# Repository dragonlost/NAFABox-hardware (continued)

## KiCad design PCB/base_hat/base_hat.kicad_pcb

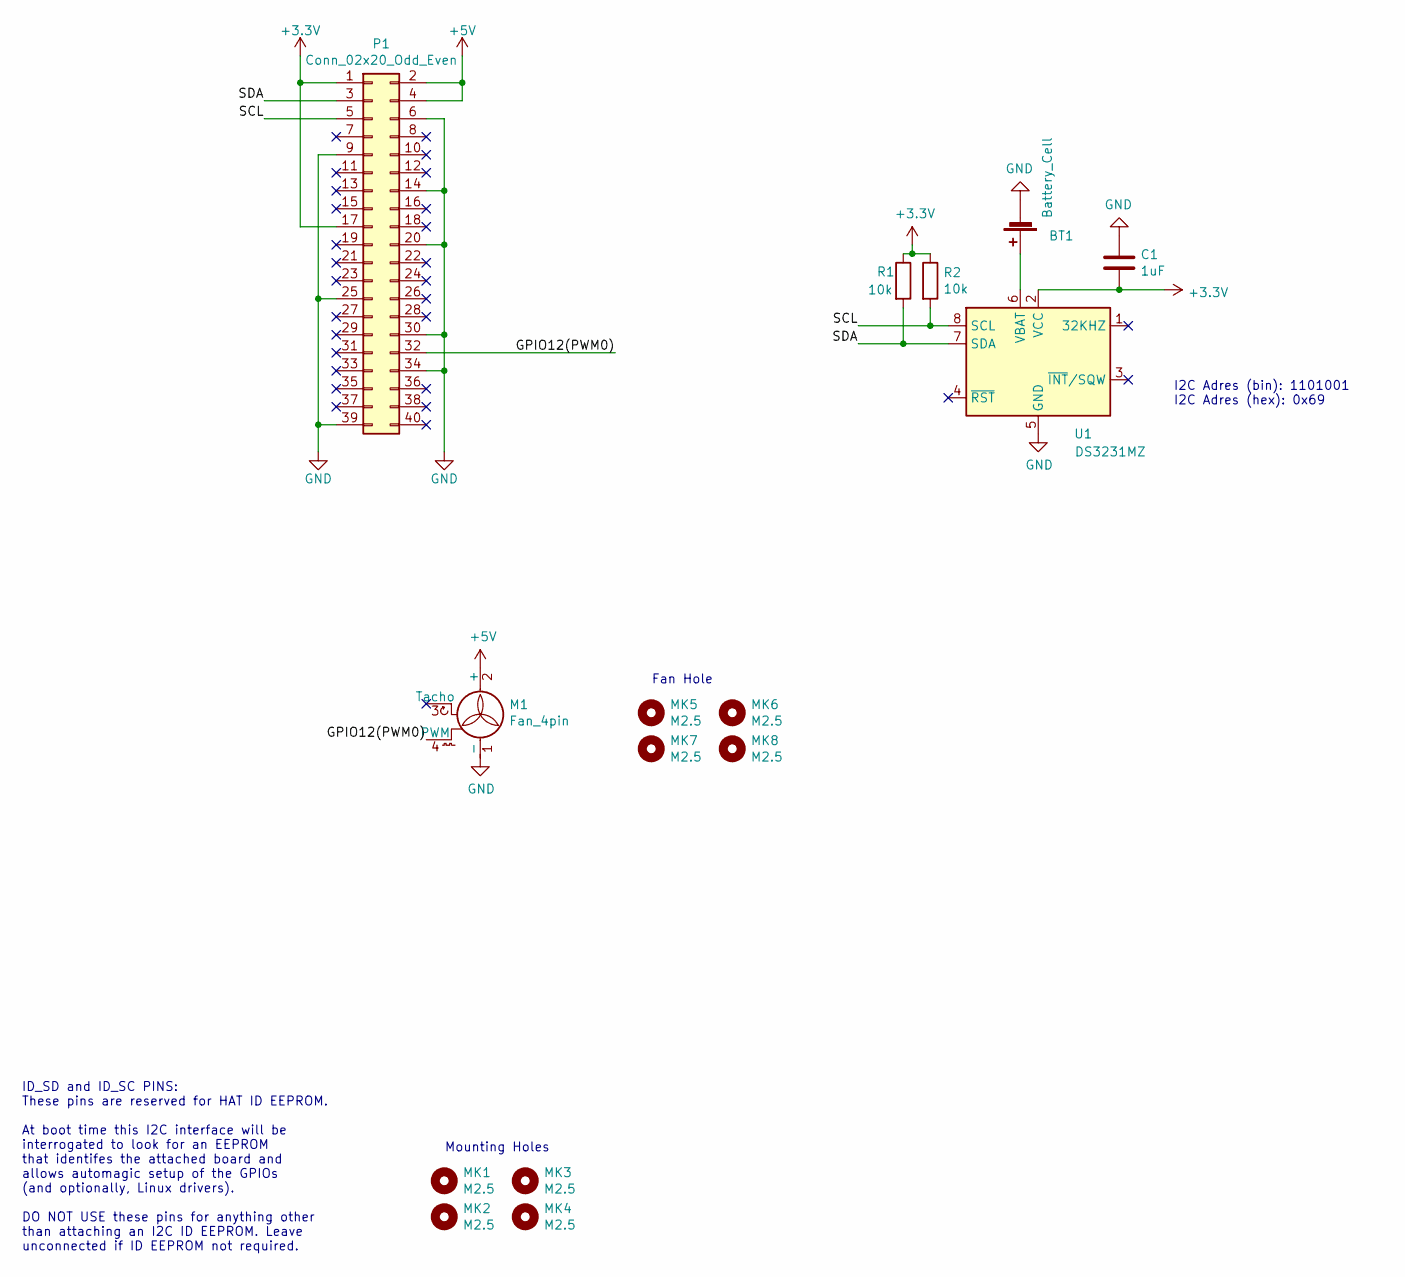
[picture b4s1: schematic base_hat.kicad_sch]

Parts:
BT1: Battery_Cell; BatteryHolder_Keystone_1060_1x2032; MF Part CR2032-BS-6-1; LCSC Part C70377
C1: 1uF; C_0805_2012Metric; MF Part 0805ZC105KAT2A; LCSC C179466
M1: Fan_4pin; PinHeader_1x04_P2.54mm_Vertical; MF Part 640456-4; LCSC Part C86504
MK1, MK2, MK3, MK4, MK5, MK6, MK7, MK8: M2.5; MountingHole_2.7mm_M2.5
P1: Conn_02x20_Odd_Even; PinSocket_2x20_P2.54mm_Vertical; MF Part C35165; LCSC Part C35165
R1, R2: 10k; R_0805_2012Metric; MF Part RT0805DRD0710KL; LCSC C17414
U1: DS3231MZ; SOIC-8_3.9x4.9mm_P1.27mm; MF Part DS3231MZ+TRL; LCSC C107410

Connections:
+3.3V: C1.2, P1.1, P1.17, R1.1, R2.1, U1.2 (VCC)
+5V: M1.2 (+), P1.2, P1.4
/GPIO12(PWM0): M1.4 (PWM), P1.32
/SCL: P1.5, R2.2, U1.8 (SCL)
/SDA: P1.3, R1.2, U1.7 (SDA)
GND: BT1.2 (-), C1.1, M1.1 (-), P1.6, P1.9, P1.14, P1.20, P1.25, P1.30, P1.34, P1.39, U1.5 (GND)
unnamed: BT1.1 (+), U1.6 (VBAT)

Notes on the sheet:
ID_SD and ID_SC PINS: These pins are reserved for HAT ID EEPROM. At boot time this I2C interface will be interrogated to look for an EEPROM that identifes the attached board and allows automagic setup of the GPIOs (and optionally, Linux drivers). DO NOT USE these pins for anything other than attach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
Fan Hole
Mounting Holes
I2C Adres (bin): 1101001 I2C Adres (hex): 0x69

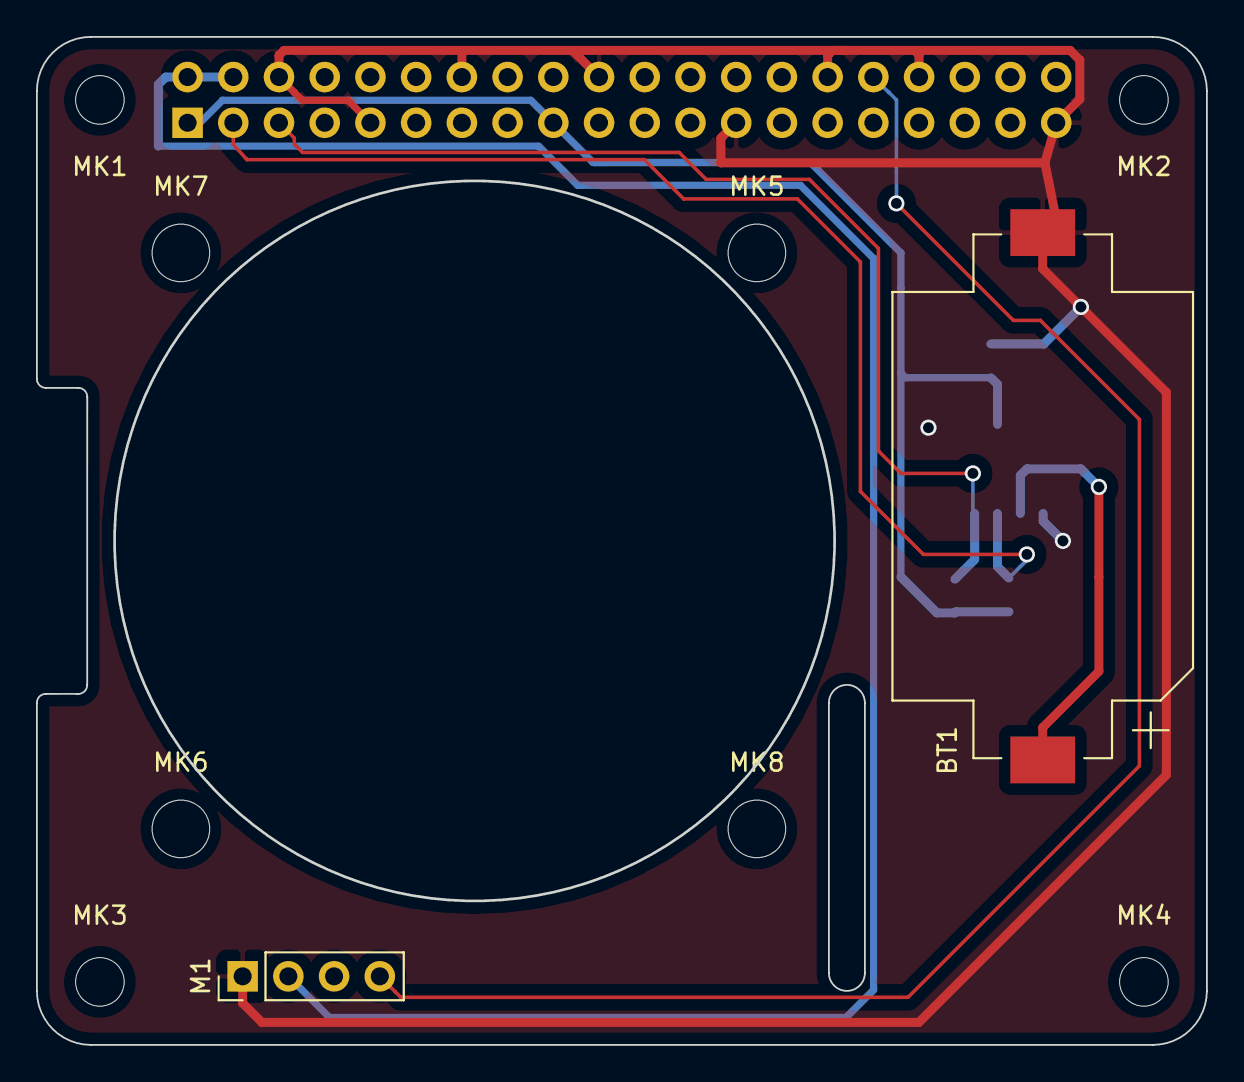
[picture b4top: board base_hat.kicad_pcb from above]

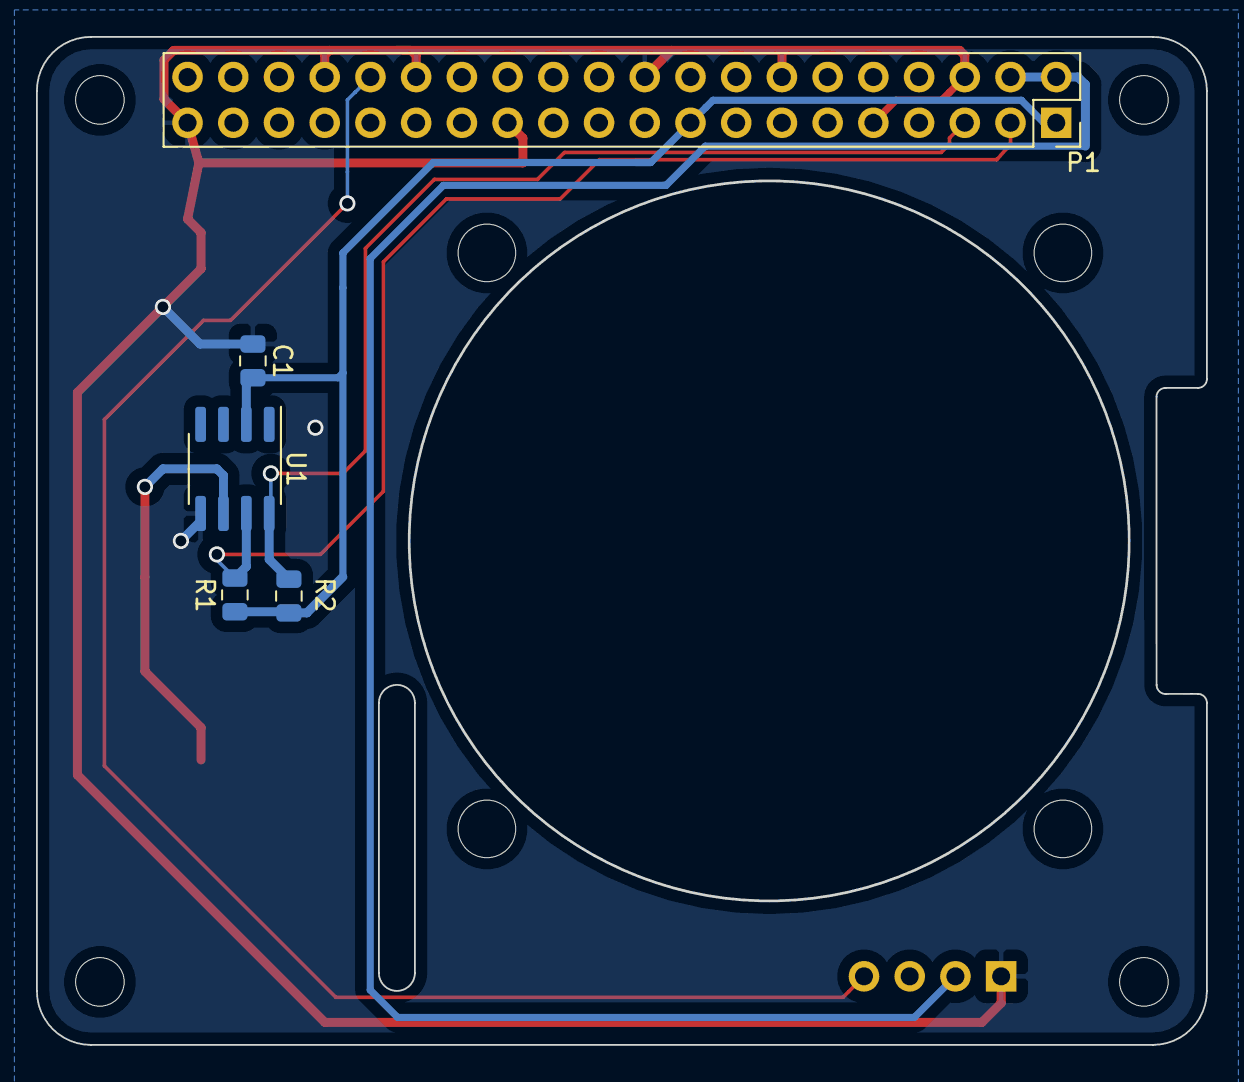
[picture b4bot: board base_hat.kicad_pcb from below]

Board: 2 copper layers, 65.0 x 56.0 mm, 15 parts (5 on the bottom side), 7 nets.

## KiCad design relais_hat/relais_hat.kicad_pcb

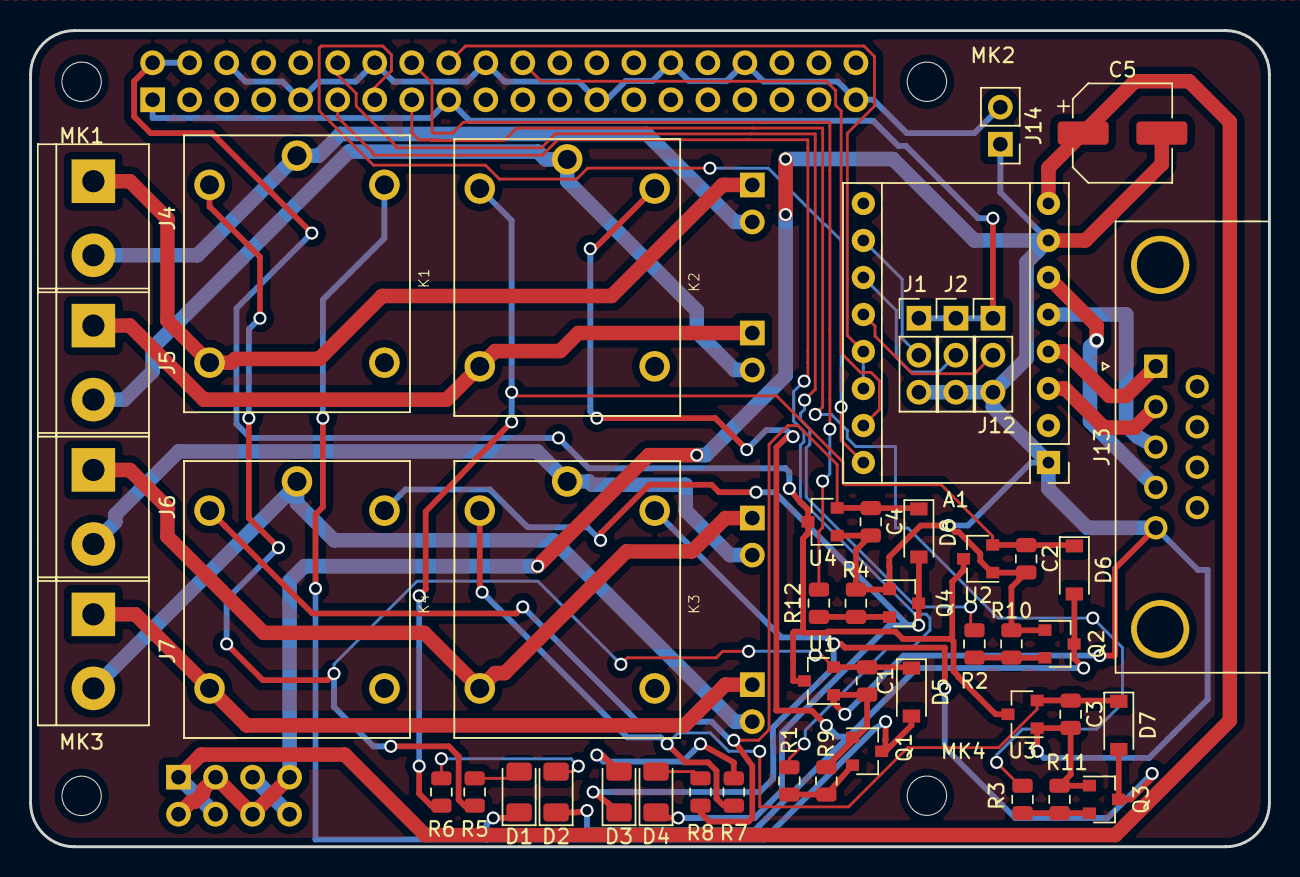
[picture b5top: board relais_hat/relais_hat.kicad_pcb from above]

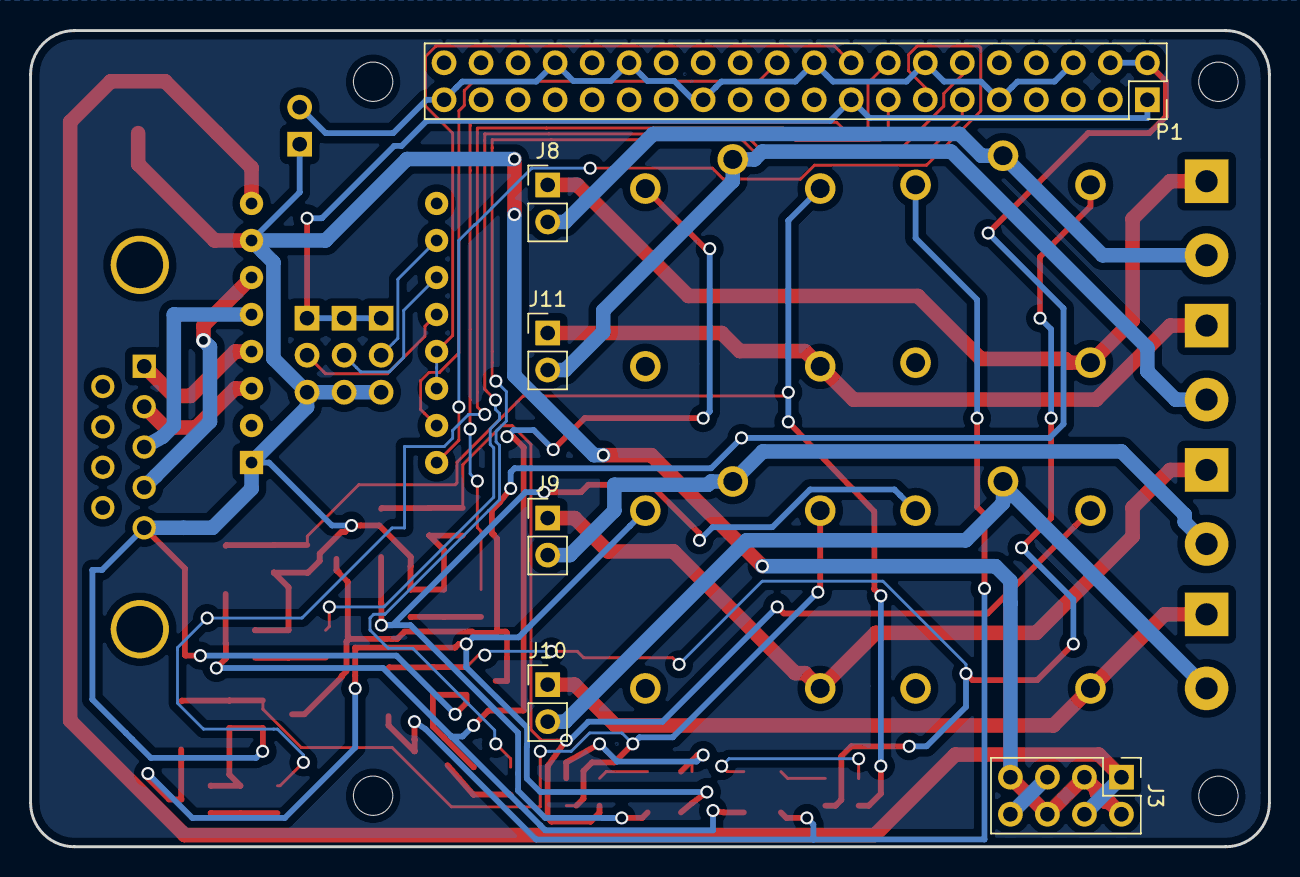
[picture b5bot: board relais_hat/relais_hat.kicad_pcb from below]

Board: 2 copper layers, 85.0 x 56.0 mm, 57 parts (6 on the bottom side), 44 nets.

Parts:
A1: Pololu_Breakout_DRV8825; Pololu_Breakout-16_15.2x20.3mm
C1, C2, C3, C4: 1uF; C_0805_2012Metric
C5: 100uF; CP_Elec_6.3x7.7
D1, D2, D3, D4: LED; LED_1206_3216Metric
D5, D6, D7, D8: 1N4148W-7-F; D_SOD-123
J1, J2, J12: Conn_01x03; PinHeader_1x03_P2.54mm_Vertical
J3: Conn_02x04_Odd_Even; PinHeader_2x04_P2.54mm_Vertical
J4, J5, J6, J7: Screw_Terminal_01x02; TerminalBlock_bornier-2_P5.08mm
J8, J9, J10, J11, J14: Conn_01x02; PinHeader_1x02_P2.54mm_Vertical
J13: DB9_Female; DSUB-9_Female_Horizontal_P2.77x2.84mm_EdgePinOffset4.94mm_H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
K1, K2, K3, K4: RELAY-HLS8L-DC3V-S-C(5P-19X15MM); REY5-19.0X15.0X15.0MM
MK1, MK2, MK3, MK4: M2.5; MountingHole_2.7mm_M2.5
P1: Conn_02x20_Odd_Even; PinSocket_2x20_P2.54mm_Vertical
Q1, Q2, Q3, Q4: S8050; SOT-23
R1, R2, R3, R4: 4.7k; R_0805_2012Metric
R5, R6, R7, R8: 470; R_0805_2012Metric
R9, R10, R11, R12: 47k; R_0805_2012Metric
U1, U2, U3, U4: XC6206P302MR-G; SOT-23

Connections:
+3V3: J1.1, J2.1, J12.1, P1.1, P1.17
+5V: P1.2, P1.4, U1.3, U2.3, U3.3, U4.3
+12V: A1.8, C5.1, J3.1, J3.4
/GPIO17: P1.11, R1.1
/GPIO18: P1.12, R2.1
/GPIO22: P1.15, R3.1
/GPIO23: P1.16, R4.1
/GPIO24: A1.13, A1.14, P1.18
/GPIO25: A1.15, P1.22
/GPIO27: A1.16, P1.13
/rpi_gnd: J14.2, P1.6, P1.9, P1.14, P1.20, P1.25, P1.30, P1.34, P1.39
GND: A1.1, A1.7, C1.2, C2.2, C3.2, C4.2, C5.2, J1.3, J2.3, J3.2, J3.3, J3.6, J3.7, J12.3, J13.5, J14.1, Q1.1, Q2.1, Q3.1, Q4.1, R9.2, R10.2, R11.2, R12.2, U1.1, U2.1, U3.1, U4.1
unnamed: A1.3, J13.2
unnamed: A1.4, J13.1
unnamed: A1.5, J13.3
unnamed: A1.6, J13.4
unnamed: A1.10, J1.2
unnamed: A1.11, J2.2
unnamed: A1.12, J12.2
unnamed: C1.1, D5.1, K1.2, R5.1, U1.2
unnamed: C2.1, D6.1, K2.2, R6.1, U2.2
unnamed: C3.1, D7.1, K3.2, R7.1, U3.2
unnamed: C4.1, D8.1, K4.2, R8.1, U4.2
unnamed: D1.1, D5.2, K1.3, Q1.3
unnamed: D1.2, R5.2
unnamed: D2.1, D6.2, K2.3, Q2.3
unnamed: D2.2, R6.2
unnamed: D3.1, D7.2, K3.3, Q3.3
unnamed: D3.2, R7.2
unnamed: D4.1, D8.2, K4.3, Q4.3
unnamed: D4.2, R8.2
unnamed: J4.1, J8.1, K1.4
unnamed: J4.2, J8.2, K1.1
unnamed: J6.1, J9.1, K3.4
unnamed: J6.2, J9.2, K3.1
unnamed: J7.1, J10.1, K4.4
unnamed: J7.2, J10.2, K4.1
unnamed: J5.1, J11.1, K2.4
unnamed: J5.2, J11.2, K2.1
unnamed: Q1.2, R1.2, R9.1
unnamed: Q2.2, R2.2, R10.1
unnamed: Q3.2, R3.2, R11.1
unnamed: Q4.2, R4.2, R12.1
VCC: J3.5, J3.8

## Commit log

2020-08-03 remove gerber
2020-08-03 create 3 folder
2020-08-03 change image position and change library to lib in res_hat
2020-08-04 update position off gps and optimise pcb
2020-08-28 clean file and genrate lastep pcb step/image/pdf
2020-08-28 first release for Readme
2020-08-28 add fab file for JLCPCB
2020-08-28 upgrade alim piste size on alim board
2020-08-30 readme correction
2020-08-30 add tab for futur BOM
2020-09-01 add lcls part number and add Fab file
2020-09-01 update/add LCSC ref and create fab file
    bug for Res_hat with JLCPCB site
2020-09-02 add res_hat fab file
2020-09-03 correct wrong ref for JLCPCB
2020-09-05 correct wring align for 4x2pin connector
2020-09-05 add new folder
2020-09-05 Add 3D view
2020-09-05 Add box drawing
2020-09-05 remove folder
2020-09-05 Add 3D models for printing
2020-09-06 rize picture
2020-09-06 add picture
2020-09-06 resize pict
2020-09-06 resize
2020-09-06 Add Box in Readme
2020-09-06 Add New View Isometric
2020-09-06 Add new drawing overall
2020-09-22 warning : correct big error on alim hat
2020-09-22 change connector type
2020-09-29 New revision
    Update +2mm over RPI fan hat
2020-09-29 New revision, and .stl files
    Update +2mm over RPI fan hat
2020-09-29 Add Carter RPI
2020-09-29 Add new casing isometric view
    old : ![Iso_compil](https://github.com/dragonlost/NAFABox-hardware/raw/master/Doc/picture/Iso_compil.jpg)
2020-09-29 Add .stl file of SD cover
2020-10-04 Q1/2/3/4 orientation correction
2020-10-08 change led color for red
2020-10-08 correct wrong R4/R12 position
2020-10-12 add hexa i2c adress
2020-10-24 change DC for XT30, change controle res for pwm
    add ds1050Z-025+ change for xt30 connector for in alim
2020-10-24 add serigraph and update name for componant
2020-10-24 add 3d model for xt30
2020-10-25 complet new polarity protection
    update fab file
2020-10-29 update alim and relais pcb 2-> 4 couches
2020-10-29 update 3d model and fab file for all board
2020-10-29 ajust skills for alim board
2020-10-30 ajust all board
2020-10-30 add second trace for big fuse
2020-10-30 update ref for relais hate
2020-11-13 ajust terminal position in relay board
    change hole diameter in res_board
2020-11-13 update terminal 3d
2020-11-13 add jack dc for res-hate 3d modem
2020-11-13 Add new drawing revision
2020-11-13 Add new revison
2020-11-18 invert polarity xt30 connector
2020-11-19 first python software version
2020-12-27 change relay to mofset
2020-12-27 add 3D xt30 model
2020-12-27 add temp 1-wire in db9 connector
2020-12-27 add relay shell instruction and correction for script+ina219
    remove wrong script
2020-12-28 add ds1050 lib
2020-12-28 correct ds1050 lib
2020-12-28 add python prog for relay
2021-01-14 change capo design
2021-02-10 New revision
    change hole of the nut, the height of RPI's carter, the height of the cover, length of the SD cover
2021-02-10 Add new revision drawing
2021-04-23 add R 10k on source/gate
2021-04-23 change 12v to GND Jack DC cut-off
2021-04-26 add pin header for inject 5V in VCC
2021-04-27 correcte R100ohms ref on BOM
2021-04-28 Add mounting holes isolation
2021-04-28 Correct labels error of cross jumpers
2021-04-28 Add alim_hat tests
2021-04-28 Add base_hat tests
2021-04-28 Add relais_hat tests
2021-04-28 Add res_hat tests
2021-06-08 update gerber for alim hat
2021-06-08 Add BOM for other part alim_board
2021-07-15 change trace for CP capa
    help jlcpcb analyse
2021-11-21 update picture
2022-08-30 Update BOM_base_hat_JLCPCB.csv
    change capa for basic part
2023-06-01 upgrade res hat to kicad 7.0
2023-06-01 upgarde alim hat to kicad 7.0
2023-06-01 upgrade relais hat and all hat to kicad 7.0
2023-11-12 add fan speed log
2023-11-13 Firste temporary release.
2023-11-13 iaddons
2023-11-14 Reqork for synthesis of intensity requirements.
2023-11-20 update.
2023-11-26 Traveaux sur les composants les modes d'utilisations, et sur la compatibilité.
2023-12-29 Corrections diverses introduction d'éléments de conception.
2024-01-03 New release.
2024-01-03 Add main for demo in libs. Remobve unneeded depende,cies. Add example.
2024-01-03 Add examples.
